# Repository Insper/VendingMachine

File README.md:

# Insper Filament Vending Machine 

This is the repository of the Insper filament vending machine.

The first go of this machine was to demonstrate to undergraduate students that are attending the embedded computer course (Insper Computer Engineering) an demo of what they should do on the first (of two) projects of this course. On this project they should specify and develop an autonomous machine that sells something.

Looking for some real need of a vending machine on Insper, we decided together if Insper-Fablab to "sell"  filaments for the 3D printers. 

Insper Fablab was response for all the mechanical part (project and fabrication). Insper Computer Architecture Lab for the specification, assemble and firmware development.

Now that we have a first prototype we detect several improvements to the machine on several areas: Usability, Mechanical and Firmware. We start to specify a second version that shall be put under real test.

# Technical

This machine is controlled by a Microchip Cortex M7 uC (SAME70) and runs a freertos to control all peripherals: 

- LCD
- Keypad
- bluetooth communication
- two step motors
- RGB LED strips

---------------------------
- UNDER CONSTRUCTION 
---------------------------

```

#############################################################
#############################################################
##               --  EXT1 LCD maXTouch Xplained --         ##
##                                                         ##
##                        \/                               ##
##                        ID    GND                        ##
##               (**NC**) PC31  PA19 (**NC**)              ##
##                 (GPIO) PB3   PB2  (**NC**)              ##
##                  (PWM) PA0   PC30 (**NC**)              ##
##             (GPIO/IRQ) PD28  PC17 (GPIO)                ##
##            (I²C - SDA) PA3   PA4  (I²C - SCL)           ##
##               (**NC**) PB0   PB1  (**NC**)              ##
##             (SPI MISO) PD25  PD21 (SPI SCK)             ##
##        (Botão Direita) PD20  PD22 (Botão Baixo)         ##
##                        GND   VCC                        ##
##                                                         ##
#############################################################
#############################################################

#############################################################
#############################################################
##              --  J500 - Motor Driver 2  --              ##
##                                                         ##
##               \/                                        ##
##                                                         ##
##               AREF (AREF) - (**NC**)                    ##
##               GND   (GND) - (GND)                       ##
##               D13  (PD22) - (EN_B - Motor 2)            ##
##               D12  (PD20) - (EN_A - Motor 2)            ##
##               D11  (PD21) - (IN2_B - Motor 2)           ##
##               D10  (PD25) - (IN1_B - Motor 2)           ##
##               D9    (PC9) - (IN2_A - Motor 2)           ##
##               D8   (PA17) - (IN1_A - Motor 2)           ##
##                                                         ##
##                                                         ##
#############################################################
#############################################################

#############################################################
#############################################################
##              --  J503 - Motor Driver 1  --              ##
##                                                         ##
##               \/                                        ##
##                                                         ##
##               D7  (PA2) - (EN_B - Motor 1)              ##
##               D6 (PD19) - (EN_A - Motor 1)              ##
##               D5 (PD11) - (IN2_B - Motor 1)             ##
##               D4 (PD27) - (IN1_B - Motor 1)             ##
##               D3  (PA6) - (IN2_A - Motor 1)             ##
##               D2  (PA5) - (IN1_A - Motor 1)             ##
##               D1 (PD30) - (**NC**)                      ##
##               D0 (PD28) - (**NC**)                      ##
##                                                         ##
##                                                         ##
#############################################################
#############################################################

```

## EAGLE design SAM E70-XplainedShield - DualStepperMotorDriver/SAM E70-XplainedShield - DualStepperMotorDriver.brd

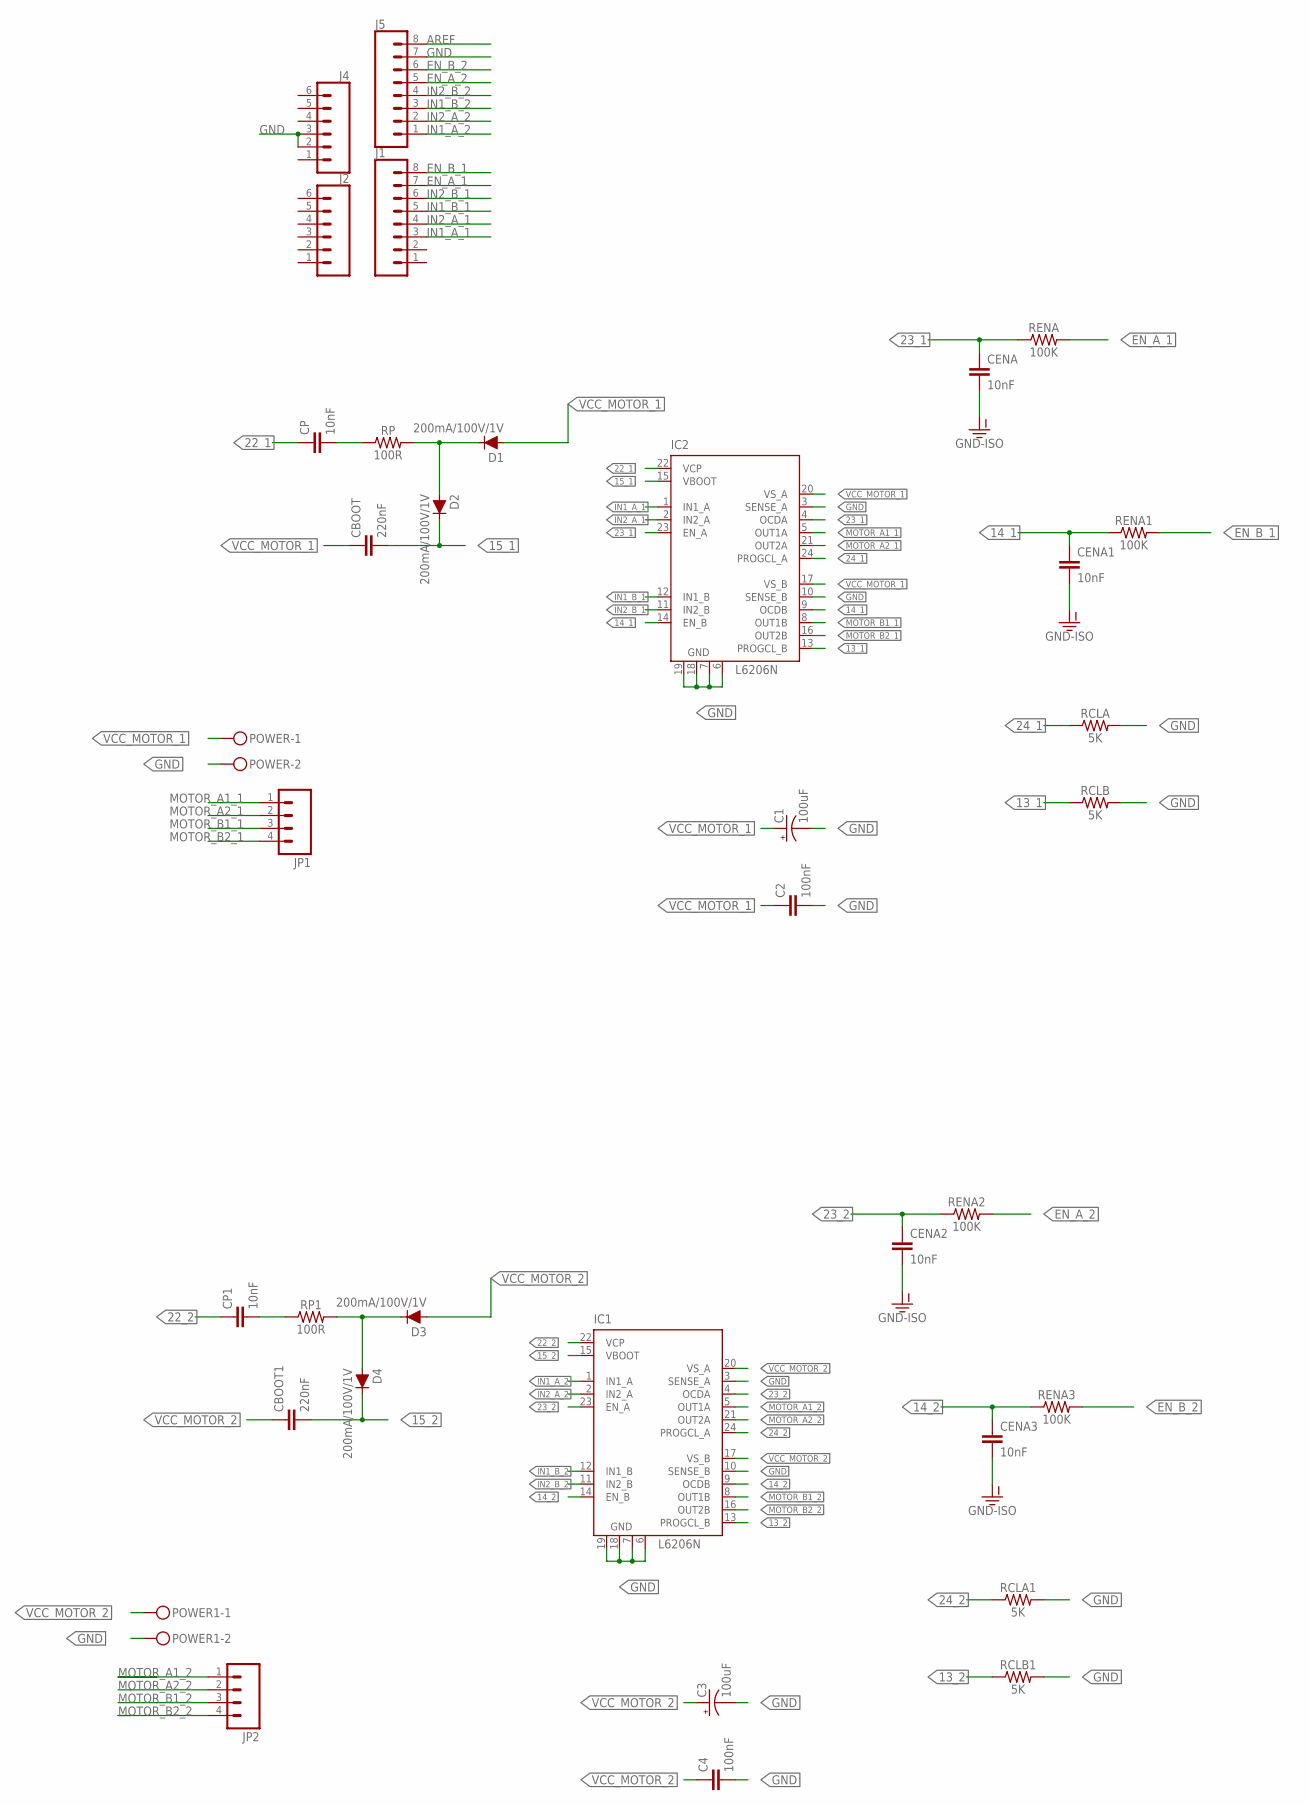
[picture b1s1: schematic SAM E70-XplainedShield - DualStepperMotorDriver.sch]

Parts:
C1, C3: 100uF; CPOL-RADIAL-100UF-25V
C2, C4: 100nF; CAP-PTH-SMALL-KIT
CBOOT, CBOOT1: 220nF; CAP-PTH-SMALL-KIT
CENA, CENA1, CENA2, CENA3: 10nF; CAP-PTH-SMALL-KIT
CP, CP1: 10nF; CAP-PTH-SMALL-KIT
D1, D2, D3, D4: 200mA/100V/1V; DIODE-1N4148
IC1, IC2: L6206N; DIL24S
J1, J5: CONN_08LONGPADS; 1X08_LONGPADS
J2, J4: CONN_06LONGPADS; 1X06_LONGPADS
JP1, JP2: M04LONGPADS; 1X04_LONGPADS
POWER, POWER1: MKDSN1,5/2-5,08
RCLA, RCLA1: 5K; AXIAL-0.3-KIT
RCLB, RCLB1: 5K; AXIAL-0.3-KIT
RENA, RENA1, RENA2, RENA3: 100K; AXIAL-0.3-KIT
RP, RP1: 100R; AXIAL-0.3-KIT

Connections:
13_1: IC2.13 (PROGCL_B), RCLB.P$1 (1)
13_2: IC1.13 (PROGCL_B), RCLB1.P$1 (1)
14_1: CENA1.1, IC2.9 (OCDB), IC2.14 (EN_B), RENA1.P$1 (1)
14_2: CENA3.1, IC1.9 (OCDB), IC1.14 (EN_B), RENA3.P$1 (1)
15_1: CBOOT.2, D2.C, IC2.15 (VBOOT)
15_2: CBOOT1.2, D4.C, IC1.15 (VBOOT)
22_1: CP.1, IC2.22 (VCP)
22_2: CP1.1, IC1.22 (VCP)
23_1: CENA.1, IC2.4 (OCDA), IC2.23 (EN_A), RENA.P$1 (1)
23_2: CENA2.1, IC1.4 (OCDA), IC1.23 (EN_A), RENA2.P$1 (1)
24_1: IC2.24 (PROGCL_A), RCLA.P$1 (1)
24_2: IC1.24 (PROGCL_A), RCLA1.P$1 (1)
AREF: J5.8
EN_A_1: J1.7, RENA.P$2 (2)
EN_A_2: J5.5, RENA2.P$2 (2)
EN_B_1: J1.8, RENA1.P$2 (2)
EN_B_2: J5.6, RENA3.P$2 (2)
GND: C1.2 (-), C2.2, C3.2 (-), C4.2, CENA.2, CENA1.2, CENA2.2, CENA3.2, IC1.3 (SENSE_A), IC1.6 (GND), IC1.7 (GND), IC1.10 (SENSE_B), IC1.18 (GND), IC1.19 (GND), IC2.3 (SENSE_A), IC2.6 (GND), IC2.7 (GND), IC2.10 (SENSE_B), IC2.18 (GND), IC2.19 (GND), J4.2, J4.3, J5.7, POWER.2, POWER1.2, RCLA.P$2 (2), RCLA1.P$2 (2), RCLB.P$2 (2), RCLB1.P$2 (2)
IN1_A_1: IC2.1 (IN1_A), J1.3
IN1_A_2: IC1.1 (IN1_A), J5.1
IN1_B_1: IC2.12 (IN1_B), J1.5
IN1_B_2: IC1.12 (IN1_B), J5.3
IN2_A_1: IC2.2 (IN2_A), J1.4
IN2_A_2: IC1.2 (IN2_A), J5.2
IN2_B_1: IC2.11 (IN2_B), J1.6
IN2_B_2: IC1.11 (IN2_B), J5.4
MOTOR_A1_1: IC2.5 (OUT1A), JP1.1
MOTOR_A1_2: IC1.5 (OUT1A), JP2.1
MOTOR_A2_1: IC2.21 (OUT2A), JP1.2
MOTOR_A2_2: IC1.21 (OUT2A), JP2.2
MOTOR_B1_1: IC2.8 (OUT1B), JP1.3
MOTOR_B1_2: IC1.8 (OUT1B), JP2.3
MOTOR_B2_1: IC2.16 (OUT2B), JP1.4
MOTOR_B2_2: IC1.16 (OUT2B), JP2.4
unnamed: CP1.2, RP1.P$1 (1)
unnamed: CP.2, RP.P$1 (1)
unnamed: D1.C, D2.A, RP.P$2 (2)
unnamed: D3.C, D4.A, RP1.P$2 (2)
VCC_MOTOR_1: C1.1 (+), C2.1, CBOOT.1, D1.A, IC2.17 (VS_B), IC2.20 (VS_A), POWER.1
VCC_MOTOR_2: C3.1 (+), C4.1, CBOOT1.1, D3.A, IC1.17 (VS_B), IC1.20 (VS_A), POWER1.1

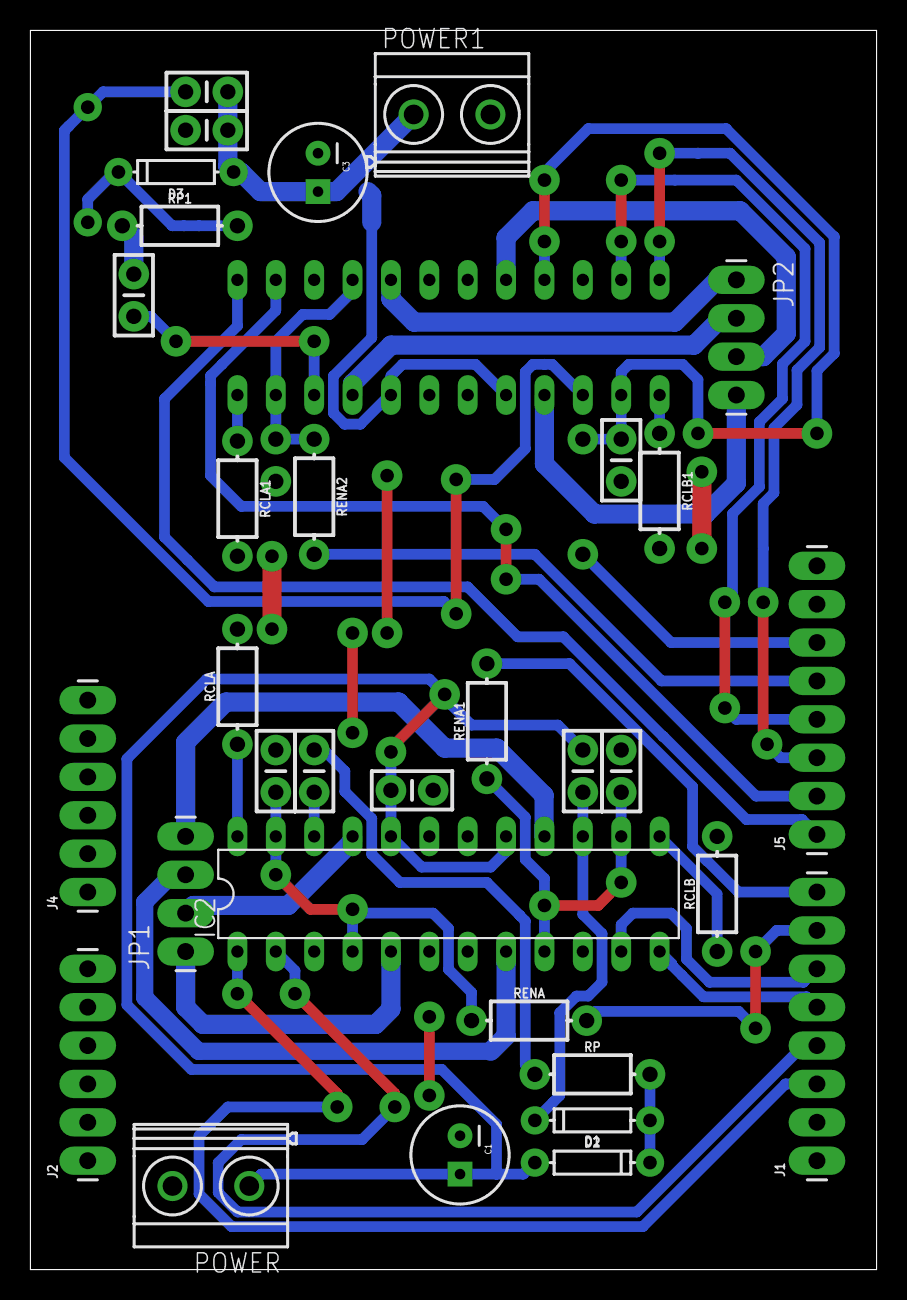
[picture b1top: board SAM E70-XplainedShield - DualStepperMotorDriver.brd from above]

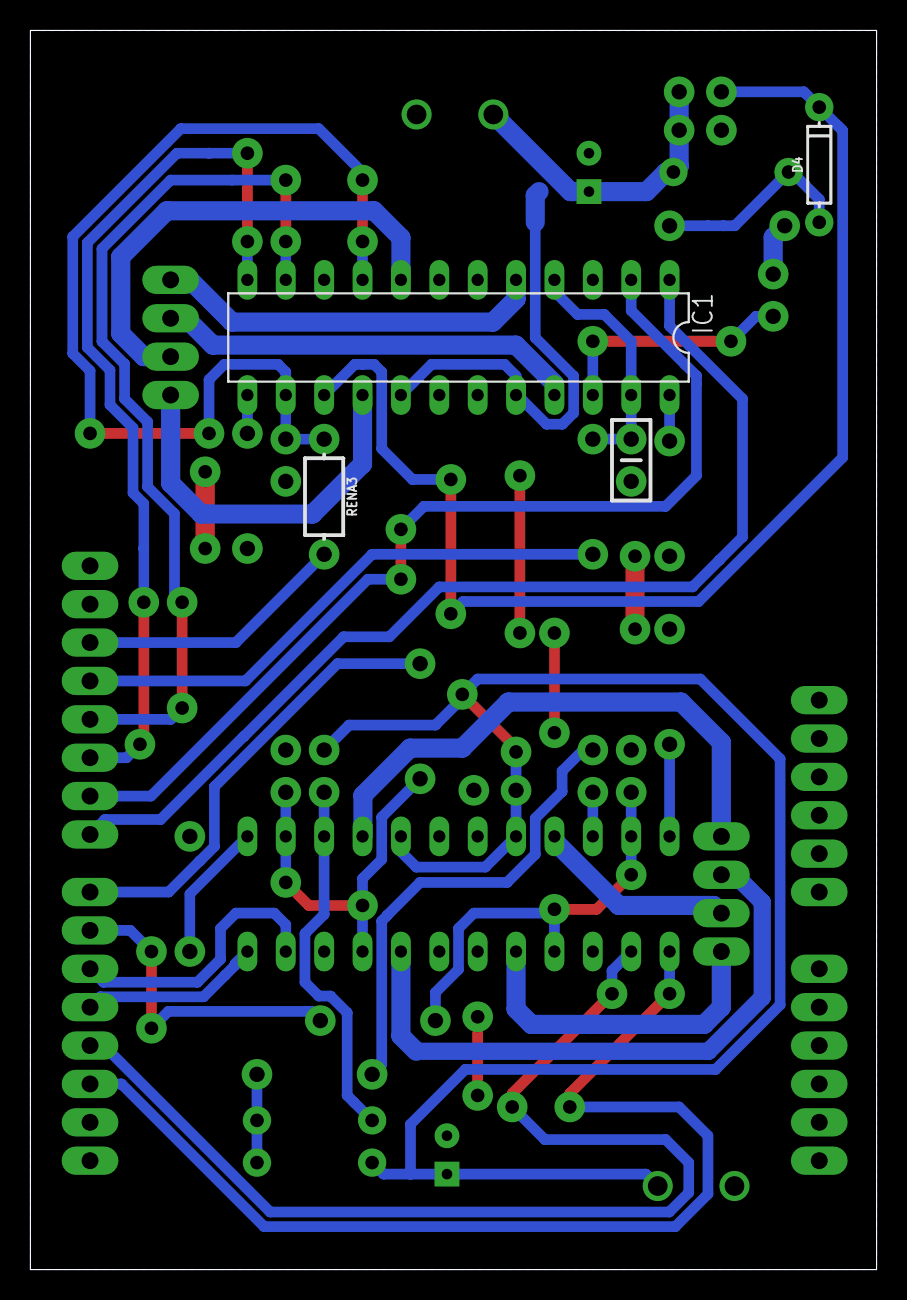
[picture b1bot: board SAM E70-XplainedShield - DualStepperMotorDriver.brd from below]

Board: 2 copper layers, 56.0 x 82.0 mm, 36 parts (4 on the bottom side), 39 nets.

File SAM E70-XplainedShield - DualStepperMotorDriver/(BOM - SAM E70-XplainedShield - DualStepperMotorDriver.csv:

Quantidade;Device;Valor;Encapsulamento;Componente;;MF;MPN;OC_FARNELL;OC_NEWARK;PROD_ID;VALUE;_
2;Barra de Pinos Fêmea;6 Vias;1x06 - Pinos Longos;J2, J4;;;;;;;;
2;Barra de Pinos Fêmea;8 Vias;1x08 - Pinos Longos ;J1, J5;;;;;;;;
2;Barra de Pinos Macho;4 Vias;1x04 - Pinos Curtos ;JP1, JP2;;;;;;;;
2;Borne KRE;2 Vias;KF301-2P;POWER, POWER1;;;;;;;;
4;Resitor ;5K;1/4W;RCLA, RCLA1, RCLB, RCLB1;;;;;; ; ;
4;Resitor;100K;1/4W;RENA, RENA1, RENA2, RENA3;;;;;; ; ;
2;Resitorr;100R;1/4W;RP, RP1;;;;;; ; ;
2;Capacitor Cerâmico;220nF;Capacitor Cerâmico Tipo Disco;CBOOT, CBOOT1;;;;;;;;
2;Capacitor Cerâmico;100nF/50V;Capacitor Cerâmico Tipo Disco;C2, C4;;;;;;;;
6;Capacitor Cerâmico;10nF/50V;Capacitor Cerâmico Tipo Disco;CENA, CENA1, CENA2, CENA3, CP, CP1;;;;;;;;
2;Capacitor Eletrolítico;100uF/25V;Capacitor Polarizado Radial;C1, C3;;;;;;;;
4;Diodo;1N4148;DO-35(DO-204AH);D1, D2, D3, D4;;;;;;DIO-08378;200mA/100V/1V;
2;DMOS dual full bridge driver;L6206;DIL24S;IC1, IC2;;;;;;;;

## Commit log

2018-10-22 22_10_2018
2018-10-22 22_10_2018_(2)
2019-02-04 Firmware 0.1 - 1 Motor Rodando
2019-02-07 Firmware de teste dos 2 motores no driver
2019-02-08 Subindo prototipos - VendingMachine
2019-02-08 Adicionando artes
2019-02-12 keypad funcionando
2019-02-13 Arrumado keypad±
2019-02-13 Antes de reorganizacao
2019-02-13 Progresso
2019-02-13 Diversas alteracoes Bluetooth, melhorias organizacao
2019-02-14 Tudo OK exceto motores
2019-02-14 Mudancas App
2019-02-14 Pinagens Shield Motores
    Acrescentado pinagens do shield dos motores
2019-02-14 Acrescentado EXT1 - LCD maXTouch
2019-02-15 Versao testada em sala
2019-02-18 Correcoes e ENABLE do Motor
2019-02-24 images v0
2019-02-24 resize
2019-07-29 Alterado e testado as pinagens (drivers de motores) e (fita de led)
2019-07-29 Retirado DualStepperMotorDriver

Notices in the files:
parts and their libraries:
SparkFun-Capacitors: Licensing: Creative Commons ShareAlike 4.0 International - https://creativecommons.org/licenses/by-sa/4.0
SparkFun-Connectors: Licensing: CC v3.0 Share-Alike You are welcome to use this library for commercial purposes.
